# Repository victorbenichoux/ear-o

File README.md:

# Project

This project describes a hearing device that can be used as a tool for embedded digital signal processing. It is based on the Ezairo chip series by ON Semi.

## Contents

The repository contains some documentation and two designs:
* A development board
* A wearable earbud

## Built With

* [Eagle CAD](https://www.autodesk.com/products/eagle/overview) - For electronic circuits and board routing.
* [Fusion 360](https://www.autodesk.com/products/fusion-360/overview) - 3D models

## Authors

* **Victor Benichoux** - *electronics and software* - Researcher at [Institut Pasteur](https://research.pasteur.fr/en/member/victor-benichoux/). Contact me if you are interested in this project.
* **Albane Imbert** - *case design* - Head of the [fab lab](https://research.pasteur.fr/en/team/fab-lab/) at Institut Pasteur.

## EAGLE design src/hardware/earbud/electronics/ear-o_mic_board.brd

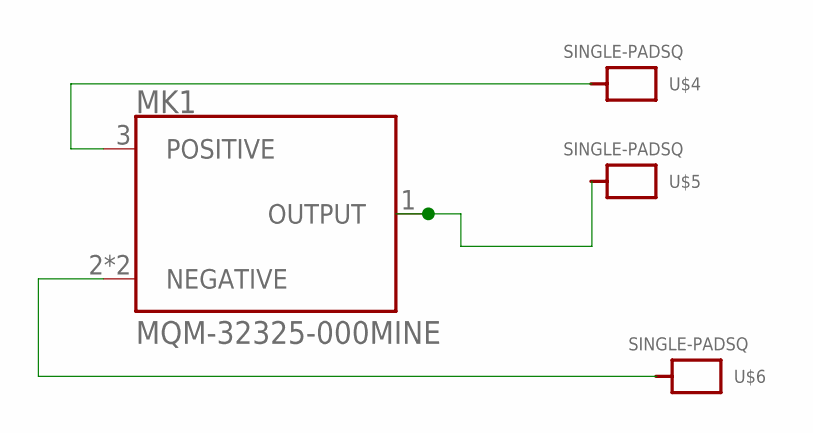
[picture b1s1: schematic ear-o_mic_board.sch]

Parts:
MK1: MQM-32325-000MINE; MIC_MINE
U$4, U$5, U$6: SINGLE-PADSQ; SQUAREPAD0.8

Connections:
NEG: MK1.2 (NEGATIVE), MK1.P$1 (NEGATIVE), U$6.P$1
POS: MK1.3 (POSITIVE), U$4.P$1
SIG: MK1.1 (OUTPUT), U$5.P$1

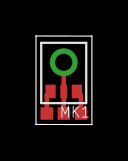
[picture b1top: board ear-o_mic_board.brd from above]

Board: 1 copper layer, 3.1 x 4.9 mm, 4 parts (0 on the bottom side), 3 nets.

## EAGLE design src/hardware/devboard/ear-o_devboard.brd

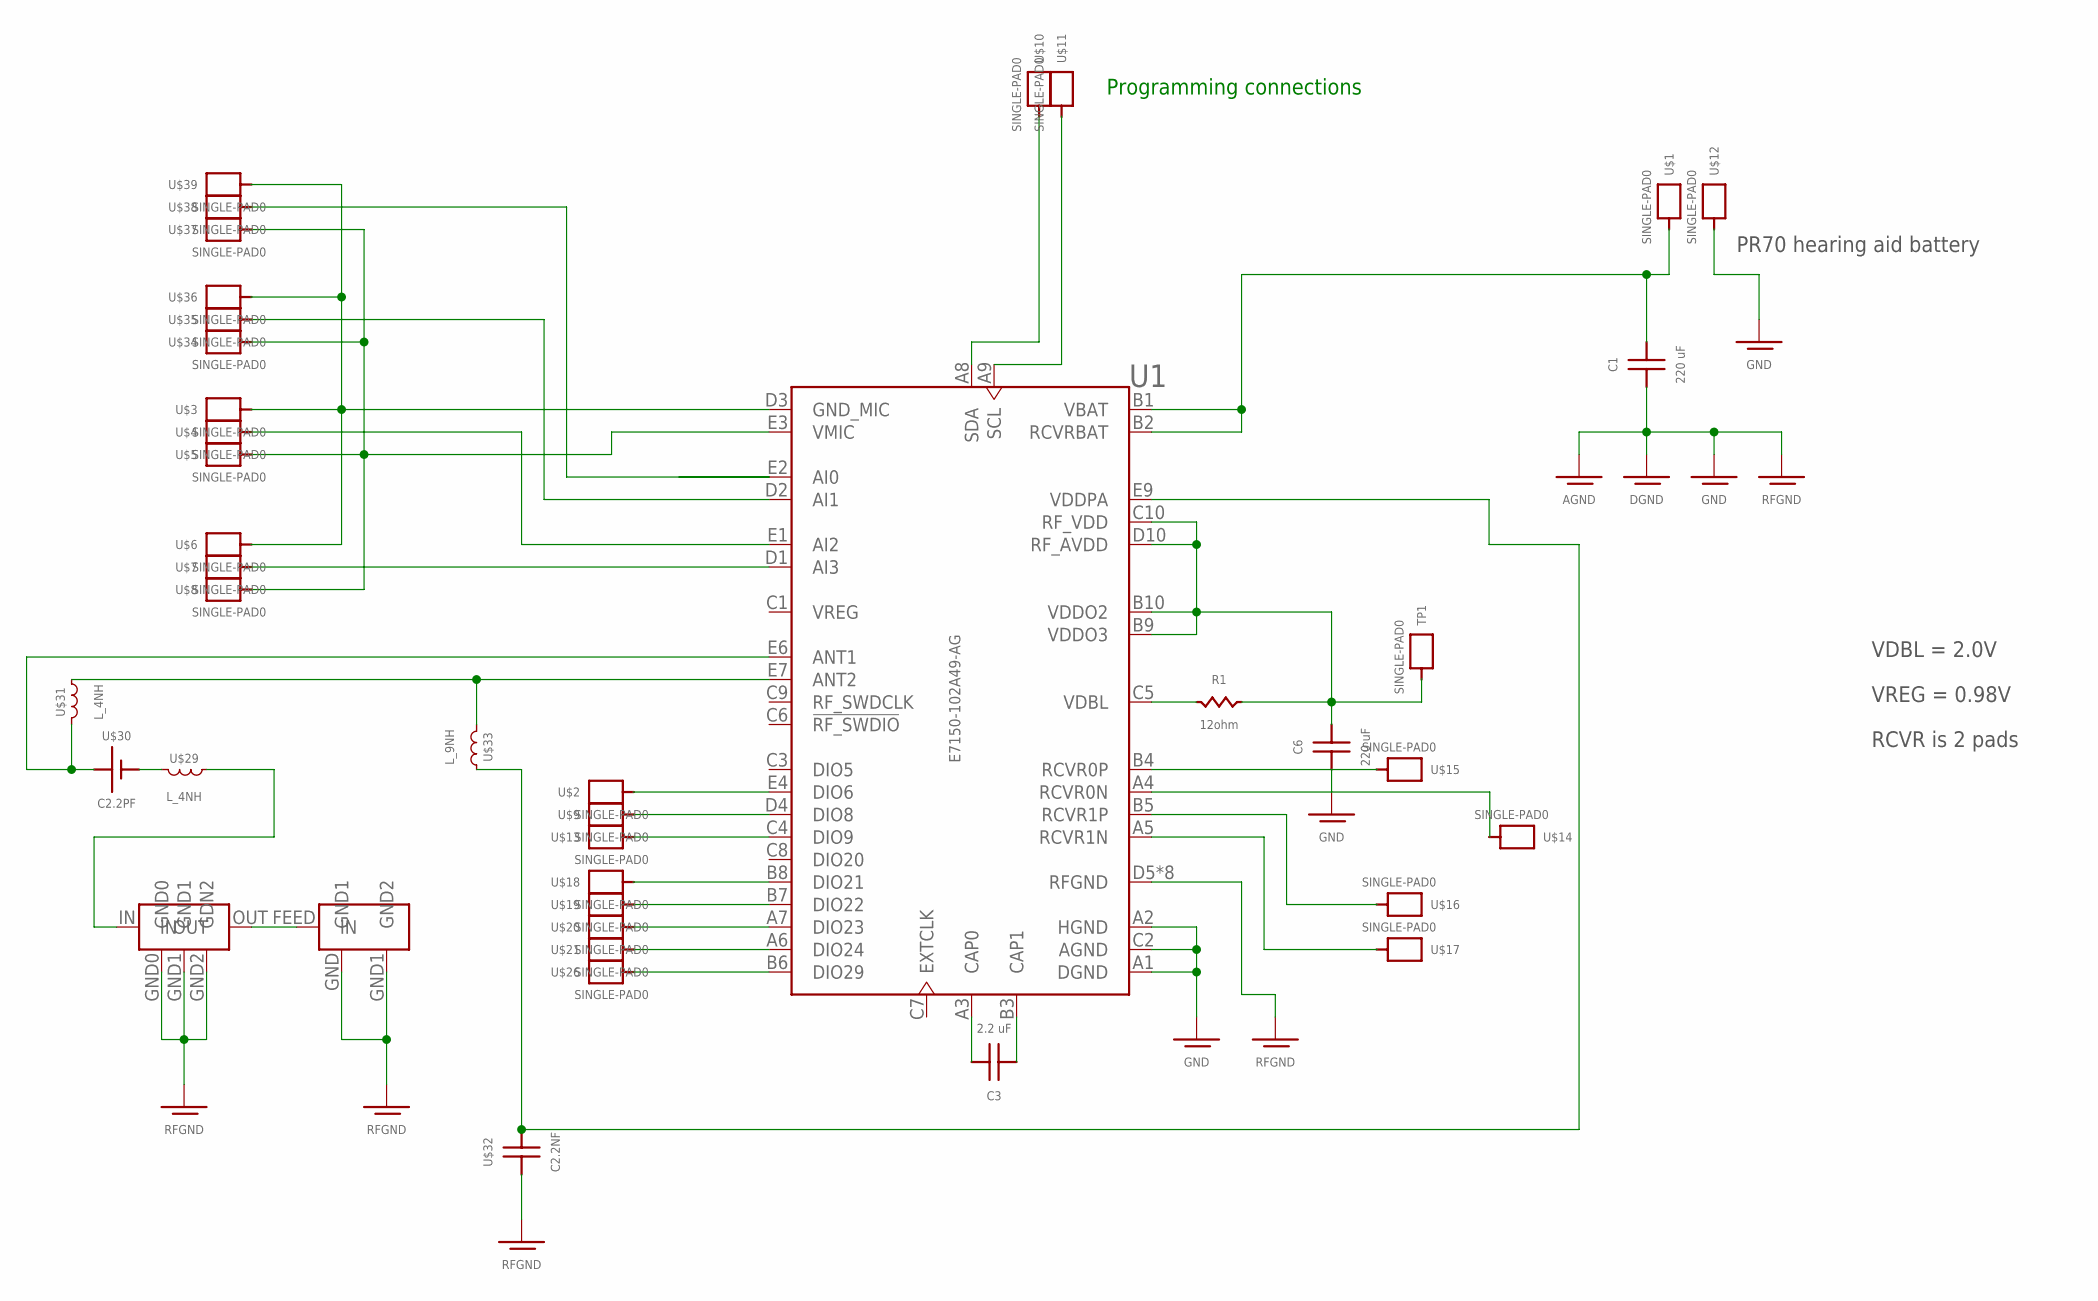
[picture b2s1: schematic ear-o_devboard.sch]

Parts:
C1, C6: 220 uF; 1206
C3: 2.2 uF; 0201
R1: 12ohm; 0201
TP1: SINGLE-PAD0; TH
U1: E7150-102A49-AG; BGA49C69P10X5_739X394X178
U$1, U$2, U$3, U$4, U$5, U$6, U$7, U$8, U$9, U$10, U$11, U$12, U$13, U$14, U$15, U$16, U$17, U$18, U$19, U$20, U$21, U$26, U$34, U$35, U$36, U$37, U$38, U$39: SINGLE-PAD0; TH
U$27: CHIP_ANT; W3008
U$28: RF_FILT; BPFILT
U$29, U$31: L_4NH; 0402
U$30: C2.2PF; 0201
U$32: C2.2NF; 0201
U$33: L_9NH; 0402

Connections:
1.4V: C1.P$2 (2), U1.B1 (VBAT), U1.B2 (RCVRBAT), U$1.P$1
DIO6: U1.E4 (DIO6), U$2.P$1
DIO8: U1.D4 (DIO8), U$9.P$1
DIO9: U1.C4 (DIO9), U$13.P$1
DIO21: U1.B8 (DIO21), U$18.P$1
DIO22: U1.B7 (DIO22), U$19.P$1
DIO23: U1.A7 (DIO23), U$20.P$1
DIO24: U1.A6 (DIO24), U$21.P$1
DIO29: U1.B6 (DIO29), U$26.P$1
MIC0S: U1.E2 (AI0), U$38.P$1
MIC1S: U1.D2 (AI1), U$35.P$1
MIC2S: U1.E1 (AI2), U$4.P$1
MIC3S: U1.D1 (AI3), U$7.P$1
MIC-N: U1.D3 (GND_MIC), U$3.P$1, U$6.P$1, U$36.P$1, U$39.P$1
MIC-P: U1.E3 (VMIC), U$5.P$1, U$8.P$1, U$34.P$1, U$37.P$1
unnamed: R1.P$1, U1.C5 (VDBL)
unnamed: C3.P$2 (2), U1.A3 (CAP0)
unnamed: C3.P$1 (1), U1.B3 (CAP1)
unnamed: U$27.FEED (IN), U$28.OUT
unnamed: U$28.IN, U$29.1
unnamed: U1.E9 (VDDPA), U$32.P$2 (2), U$33.1
unnamed: U1.E7 (ANT2), U$31.1, U$33.2
P1.4V: U1.E6 (ANT1), U$30.P$2 (P1.4V), U$31.2
RCVR0N: U1.A4 (RCVR0N), U$14.P$1
RCVR0P: U1.B4 (RCVR0P), U$15.P$1
RCVR1N: U1.A5 (RCVR1N), U$17.P$1
RCVR1P: U1.B5 (RCVR1P), U$16.P$1
RFGND: C1.P$1 (1), C6.P$1 (1), U1.A1 (DGND), U1.A2 (HGND), U1.C2 (AGND), U1.D5 (RFGND), U1.D6 (RFGND), U1.D7 (RFGND), U1.D8 (RFGND), U1.D9 (RFGND), U1.E5 (RFGND), U1.E8 (RFGND), U1.E10 (RFGND), U$12.P$1, U$27.GND (GND1), U$27.GND1 (GND2), U$28.GND0, U$28.GND1, U$28.GND2 (GDN2), U$29.2, U$30.P$1 (GND), U$32.P$1 (1)
SCL: U1.A9 (SCL), U$11.P$1
SDA: U1.A8 (SDA), U$10.P$1
VDBL: C6.P$2 (2), R1.P$2, TP1.P$1, U1.B9 (VDDO3), U1.B10 (VDDO2), U1.C10 (RF_VDD), U1.D10 (RF_AVDD)
VREG: U1.C1 (VREG)

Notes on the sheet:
VDBL = 2.0V
VREG = 0.98V
PR70 hearing aid battery
RCVR is 2 pads
Programming connections

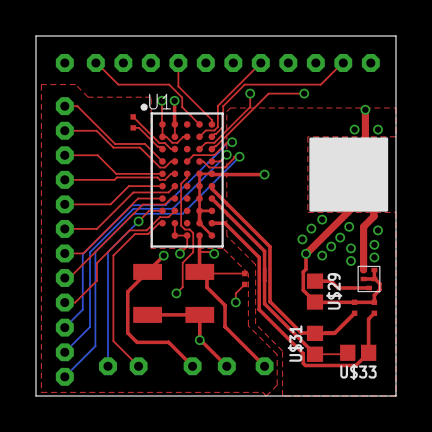
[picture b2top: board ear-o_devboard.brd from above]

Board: 4 copper layers, 20.0 x 20.0 mm, 41 parts (0 on the bottom side), 31 nets.

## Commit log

2018-01-26 Added README
2018-01-31 Added initial case design files
2018-01-31 moved the electronics to a new folder
2018-01-31 Updated the mic board datasheet
2018-01-31 Updated the README
2018-01-31 Added logo to README
2018-01-31 centering logo
2018-01-31 editing README
2018-01-31 fixing README
